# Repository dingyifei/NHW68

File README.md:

# Not Hand Wired 68 Keys

## License

This project (not include ./hardware/KiCad/, ./code, or files with licenses inside them) is using MIT license.

If not specified, the files in ./code are GPL V2

## Code

Code should be functional, haven't push it to QMK or tested on the keyboard yet, compile passed.

## Hardware

I'm attempting to draw the PCB and its my first time drawing a PCB so 0 confidence it will work. I did my research and if you want to use it plz do your own research make sure it works.

I have not yet tested the PCB, the keyboard PCB currently looks like this:

The keyboard uses STM32F303CCT6, IS31FL3733 and have per Key RGB. 

The RGB is optional since it can work without RGB (I believe most people can live without RGB :p)

Here is the fusion 360 3d mode, I think it is good enough

Fusion 360 Link: https://a360.co/2X8L0Fb

**Note: The screws and nuts are downloaded 3D model from misumi, license info can be found on misumi website**

## Layout

The blue keys' function depend on use case

## Assembly

Stacking: 

1. Plate(1.6mm)
2. Spacer(1.2mm)x3
3. PCB(1.6mm)
4. Nuts(2.4mm or more)
5. Spacer(1.2mm)
6. Base(1.6mm)
7. Nuts(2.4mm)

Use 16mm~18mm M3 screw and nuts should be just fine, a PCB fab usually provide 1.6mm and 1.2mm.

Note: Manually cut 2 spacer PCB can replace the 4. Nuts but it would mean you need to choose "Order 10" option in the most fabs (which would increase the difficulty in sourcing all the parts)

## Cost

5 piece of (Spacer, PCB, Plate, Base) - $70 if you choose leaded HSAL

Parts are relatively cheap and you don't have to worry about them, LCSC is a good place to get all those parts(u probably need Amazon for Kailh hot swap, DigiKey for RGB controller)

## Release V1.1 

#### Known Problems

1. Key Caps are hard to find
2. Center is 2u left
3. RGB LED footprint is WRONG and WON'T WORK

4. 0 ESD protection

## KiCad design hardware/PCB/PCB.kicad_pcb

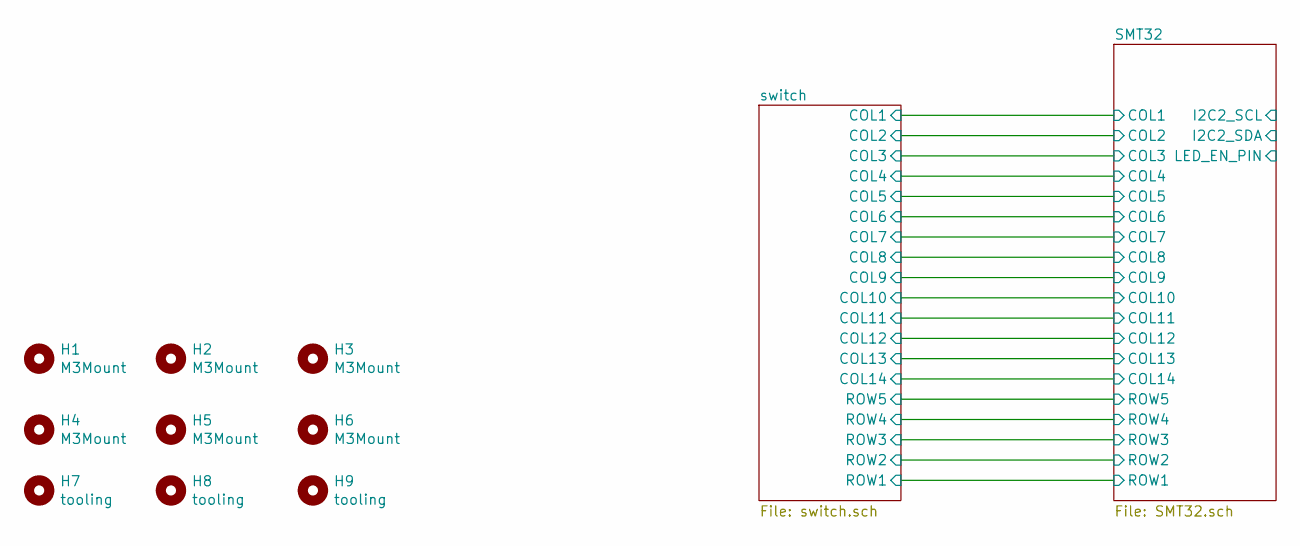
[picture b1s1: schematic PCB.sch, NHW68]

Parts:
H1, H2, H3, H4, H5, H6: M3Mount; MountingHole_3.2mm_M3_DIN965
H7, H8, H9: tooling; JLC_SMT_ToolingHole

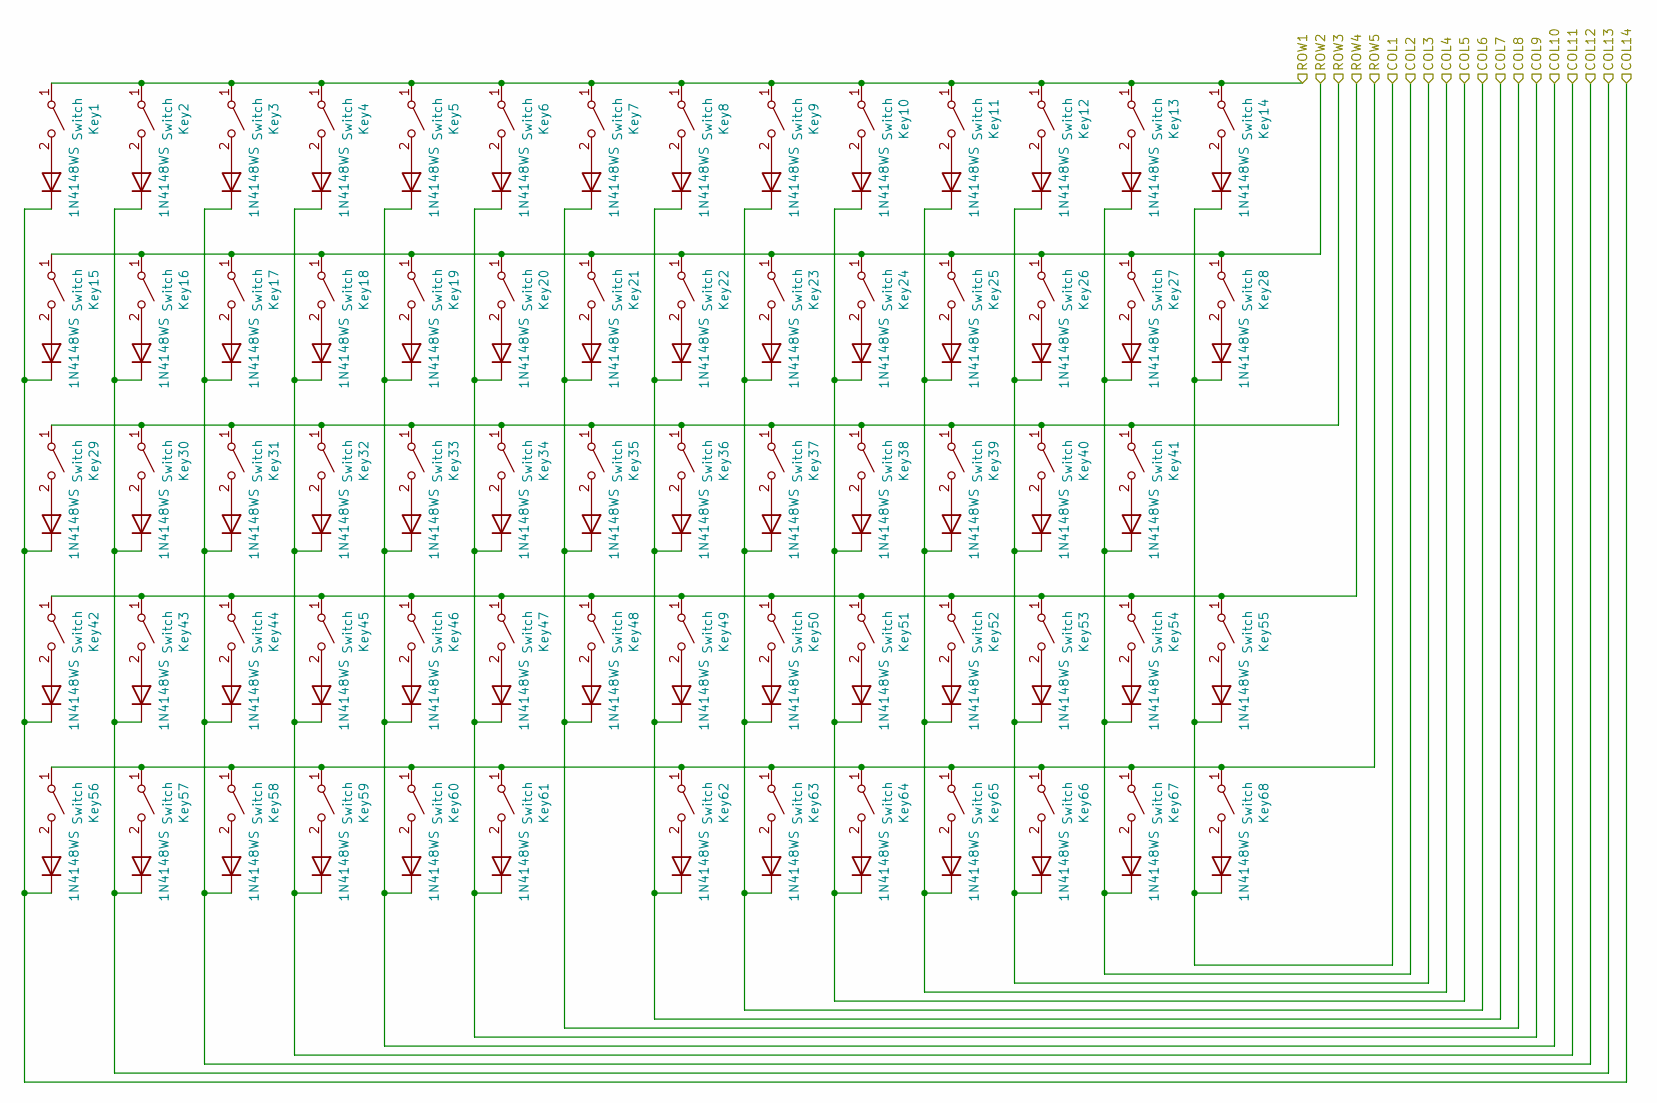
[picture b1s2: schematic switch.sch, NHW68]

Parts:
D1, D2, D3, D4, D5, D6, D7, D8, D9, D10, D11, D12, D13, D14, D15, D16, D17, D18, D19, D20, D21, D22, D23, D24, D25, D26, D27, D28, D29, D30, D31, D32, D33, D34, D35, D36, D37, D38, D39, D40, D41, D42, D43, D44, D45, D46, D47, D48, D49, D50, D51, D52, D53, D54, D55, D56, D57, D58, D59, D60, D61, D62, D63, D64, D65, D66, D67, D68: 1N4148WS; D_SOD-323; Part Number 1N4148WS; LCSC C110221
Key1, Key2, Key3, Key4, Key5, Key6, Key7, Key8, Key9, Key10, Key11, Key12, Key13, Key14, Key15, Key16, Key17, Key18, Key19, Key20, Key21, Key22, Key23, Key24, Key25, Key26, Key27, Key28, Key29, Key30, Key31, Key32, Key33, Key34, Key35, Key36, Key37, Key38, Key39, Key40, Key41, Key42, Key43, Key44, Key45, Key46, Key47, Key48, Key49, Key50, Key51, Key52, Key53, Key54, Key55, Key56, Key57, Key58, Key59, Key60, Key61, Key62, Key63, Key64, Key65, Key66, Key67, Key68: Switch; Kailh_socket_MX_simplified; Part Number CPG151101S11

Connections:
/SMT32/COL1: D14.1 (K), D28.1 (K), D55.1 (K), D68.1 (K); also elsewhere on the board
/SMT32/COL2: D13.1 (K), D27.1 (K), D41.1 (K), D54.1 (K), D67.1 (K); also elsewhere on the board
/SMT32/COL3: D12.1 (K), D26.1 (K), D40.1 (K), D53.1 (K), D66.1 (K); also elsewhere on the board
/SMT32/COL4: D11.1 (K), D25.1 (K), D39.1 (K), D52.1 (K), D65.1 (K); also elsewhere on the board
/SMT32/COL5: D10.1 (K), D24.1 (K), D38.1 (K), D51.1 (K), D64.1 (K); also elsewhere on the board
/SMT32/COL6: D9.1 (K), D23.1 (K), D37.1 (K), D50.1 (K), D63.1 (K); also elsewhere on the board
/SMT32/COL7: D8.1 (K), D22.1 (K), D36.1 (K), D49.1 (K), D62.1 (K); also elsewhere on the board
/SMT32/COL8: D7.1 (K), D21.1 (K), D35.1 (K), D48.1 (K); also elsewhere on the board
/SMT32/COL9: D6.1 (K), D20.1 (K), D34.1 (K), D47.1 (K), D61.1 (K); also elsewhere on the board
/SMT32/COL10: D5.1 (K), D19.1 (K), D33.1 (K), D46.1 (K), D60.1 (K); also elsewhere on the board
/SMT32/COL11: D4.1 (K), D18.1 (K), D32.1 (K), D45.1 (K), D59.1 (K); also elsewhere on the board
/SMT32/COL12: D3.1 (K), D17.1 (K), D31.1 (K), D44.1 (K), D58.1 (K); also elsewhere on the board
/SMT32/COL13: D2.1 (K), D16.1 (K), D30.1 (K), D43.1 (K), D57.1 (K); also elsewhere on the board
/SMT32/COL14: D1.1 (K), D15.1 (K), D29.1 (K), D42.1 (K), D56.1 (K); also elsewhere on the board
/SMT32/ROW1: Key1.1 (A), Key2.1 (A), Key3.1 (A), Key4.1 (A), Key5.1 (A), Key6.1 (A), Key7.1 (A), Key8.1 (A), Key9.1 (A), Key10.1 (A), Key11.1 (A), Key12.1 (A), Key13.1 (A), Key14.1 (A); also elsewhere on the board
/SMT32/ROW2: Key15.1 (A), Key16.1 (A), Key17.1 (A), Key18.1 (A), Key19.1 (A), Key20.1 (A), Key21.1 (A), Key22.1 (A), Key23.1 (A), Key24.1 (A), Key25.1 (A), Key26.1 (A), Key27.1 (A), Key28.1 (A); also elsewhere on the board
/SMT32/ROW3: Key29.1 (A), Key30.1 (A), Key31.1 (A), Key32.1 (A), Key33.1 (A), Key34.1 (A), Key35.1 (A), Key36.1 (A), Key37.1 (A), Key38.1 (A), Key39.1 (A), Key40.1 (A), Key41.1 (A); also elsewhere on the board
/SMT32/ROW4: Key42.1 (A), Key43.1 (A), Key44.1 (A), Key45.1 (A), Key46.1 (A), Key47.1 (A), Key48.1 (A), Key49.1 (A), Key50.1 (A), Key51.1 (A), Key52.1 (A), Key53.1 (A), Key54.1 (A), Key55.1 (A); also elsewhere on the board
/SMT32/ROW5: Key56.1 (A), Key57.1 (A), Key58.1 (A), Key59.1 (A), Key60.1 (A), Key61.1 (A), Key62.1 (A), Key63.1 (A), Key64.1 (A), Key65.1 (A), Key66.1 (A), Key67.1 (A), Key68.1 (A); also elsewhere on the board
unnamed: D1.2 (A), Key1.2 (B)
unnamed: D2.2 (A), Key2.2 (B)
unnamed: D3.2 (A), Key3.2 (B)
unnamed: D4.2 (A), Key4.2 (B)
unnamed: D5.2 (A), Key5.2 (B)
unnamed: D6.2 (A), Key6.2 (B)
unnamed: D7.2 (A), Key7.2 (B)
unnamed: D8.2 (A), Key8.2 (B)
unnamed: D9.2 (A), Key9.2 (B)
unnamed: D10.2 (A), Key10.2 (B)
unnamed: D11.2 (A), Key11.2 (B)
unnamed: D12.2 (A), Key12.2 (B)
unnamed: D13.2 (A), Key13.2 (B)
unnamed: D14.2 (A), Key14.2 (B)
unnamed: D15.2 (A), Key15.2 (B)
unnamed: D16.2 (A), Key16.2 (B)
unnamed: D17.2 (A), Key17.2 (B)
unnamed: D18.2 (A), Key18.2 (B)
unnamed: D19.2 (A), Key19.2 (B)
unnamed: D20.2 (A), Key20.2 (B)
unnamed: D21.2 (A), Key21.2 (B)
unnamed: D22.2 (A), Key22.2 (B)
unnamed: D23.2 (A), Key23.2 (B)
unnamed: D24.2 (A), Key24.2 (B)
unnamed: D25.2 (A), Key25.2 (B)
unnamed: D26.2 (A), Key26.2 (B)
unnamed: D27.2 (A), Key27.2 (B)
unnamed: D28.2 (A), Key28.2 (B)
unnamed: D29.2 (A), Key29.2 (B)
unnamed: D30.2 (A), Key30.2 (B)
unnamed: D31.2 (A), Key31.2 (B)
unnamed: D32.2 (A), Key32.2 (B)
unnamed: D33.2 (A), Key33.2 (B)
unnamed: D34.2 (A), Key34.2 (B)
unnamed: D35.2 (A), Key35.2 (B)
unnamed: D36.2 (A), Key36.2 (B)
unnamed: D37.2 (A), Key37.2 (B)
unnamed: D38.2 (A), Key38.2 (B)
unnamed: D39.2 (A), Key39.2 (B)
unnamed: D40.2 (A), Key40.2 (B)
unnamed: D41.2 (A), Key41.2 (B)
unnamed: D42.2 (A), Key42.2 (B)
unnamed: D43.2 (A), Key43.2 (B)
unnamed: D44.2 (A), Key44.2 (B)
unnamed: D45.2 (A), Key45.2 (B)
unnamed: D46.2 (A), Key46.2 (B)
unnamed: D47.2 (A), Key47.2 (B)
unnamed: D48.2 (A), Key48.2 (B)
unnamed: D49.2 (A), Key49.2 (B)
unnamed: D50.2 (A), Key50.2 (B)
unnamed: D51.2 (A), Key51.2 (B)
unnamed: D52.2 (A), Key52.2 (B)
unnamed: D53.2 (A), Key53.2 (B)
unnamed: D54.2 (A), Key54.2 (B)
unnamed: D55.2 (A), Key55.2 (B)
unnamed: D56.2 (A), Key56.2 (B)
unnamed: D57.2 (A), Key57.2 (B)
unnamed: D58.2 (A), Key58.2 (B)
unnamed: D59.2 (A), Key59.2 (B)
unnamed: D60.2 (A), Key60.2 (B)
unnamed: D61.2 (A), Key61.2 (B)
unnamed: D62.2 (A), Key62.2 (B)
unnamed: D63.2 (A), Key63.2 (B)
unnamed: D64.2 (A), Key64.2 (B)
unnamed: D65.2 (A), Key65.2 (B)
unnamed: D66.2 (A), Key66.2 (B)
unnamed: D67.2 (A), Key67.2 (B)
unnamed: D68.2 (A), Key68.2 (B)

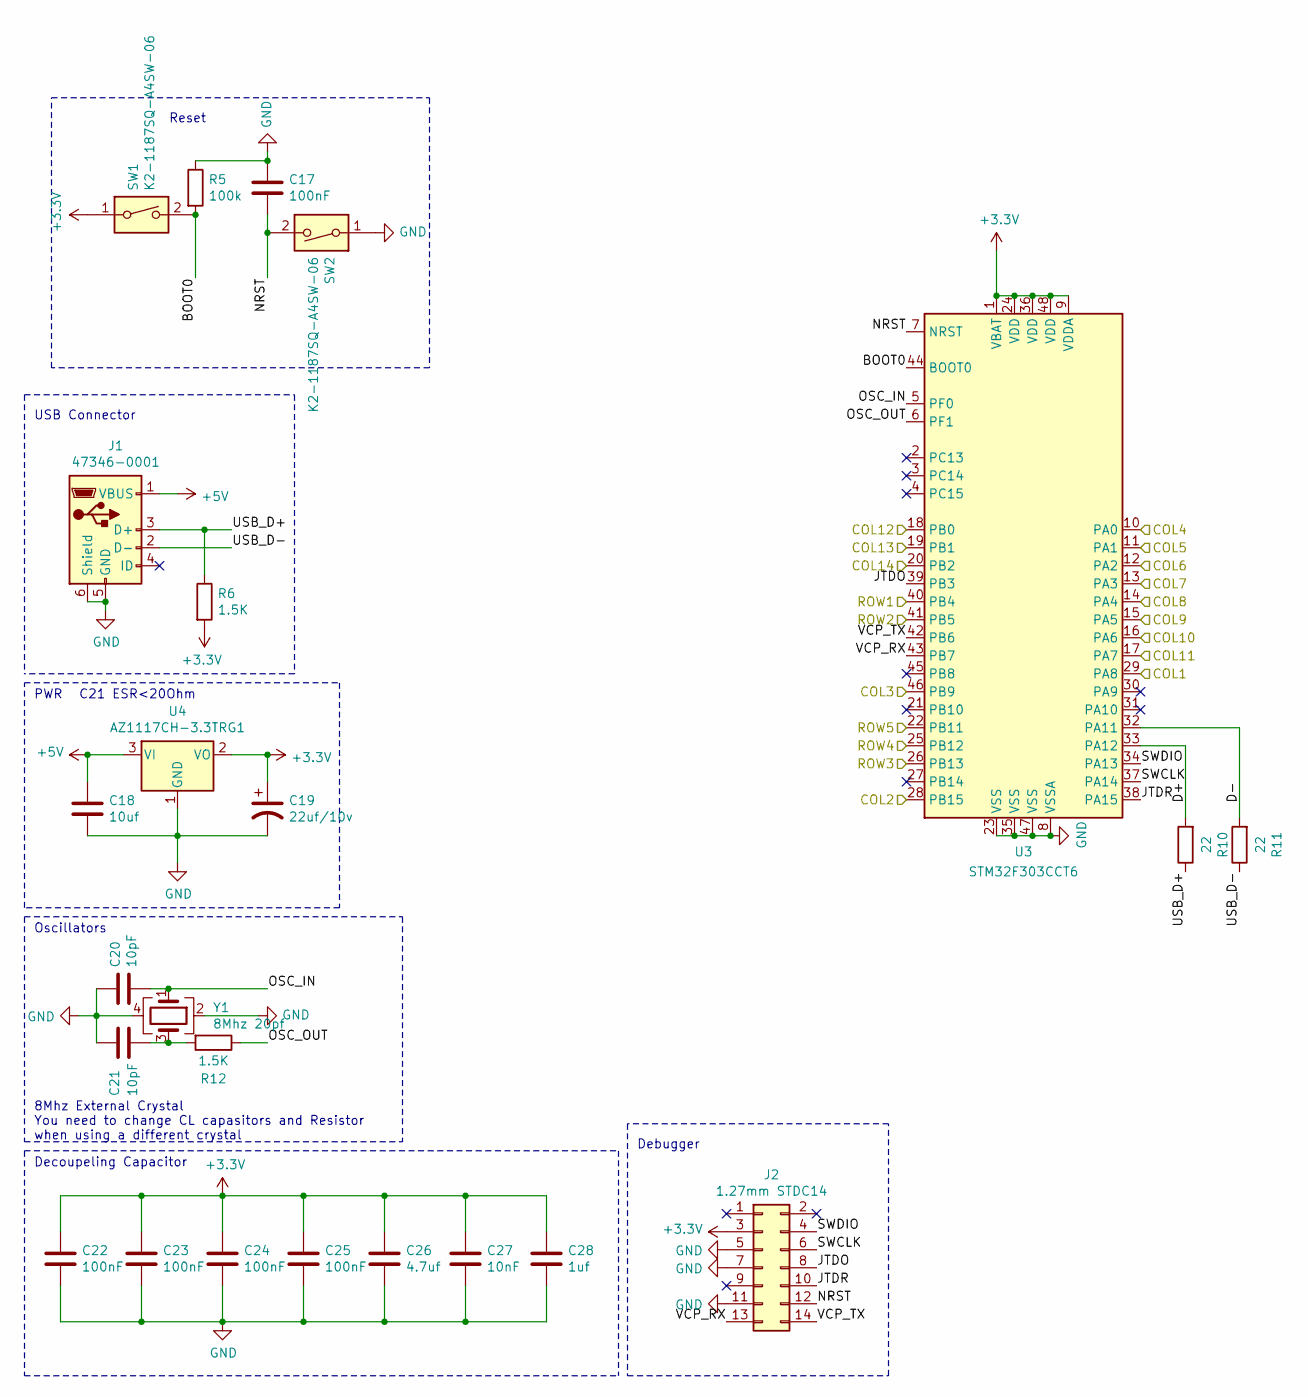
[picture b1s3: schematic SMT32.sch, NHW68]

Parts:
C17, C22, C23, C24, C25: 100nF; C_0603_1608Metric; Part Number 0603B104K160CT; LCSC C80516
C18: 10uf; C_0603_1608Metric; Part Number 0603X106K100NT; LCSC C38898
C19: 22uf/10v; CP_EIA-3216-18_Kemet-A; Part Number TAJA226K010RNJ; LCSC C11366
C20, C21: 10pF; C_0603_1608Metric; Part Number CC0603GRNPO9BN100; LCSC C325468
C26: 4.7uf; C_0603_1608Metric; Part Number CL10A475KA8NQNC; LCSC C69335
C27: 10nF; C_0603_1608Metric; Part Number CL10B103JB8NNNC; LCSC C7248
C28: 1uf; C_0603_1608Metric; Part Number UMK107AB7105KA-T; LCSC C105174
J1: 47346-0001; USB_Micro-B_Molex_47346-0001; Part Number 47346-0001; LCSC C132560
J2: 1.27mm STDC14; PinHeader_2x07_P1.27mm_Vertical
R5: 100k; R_0603_1608Metric; Part Number CR0603FA1003G; LCSC C100703
R6, R12: 1.5K; R_0603_1608Metric; Part Number RTT031501FTP; LCSC C103303
R10, R11: 22; R_0603_1608Metric; Part Number CR0603FA22R0G; LCSC C100876
SW1, SW2: K2-1187SQ-A4SW-06; Part Number K2-1187SQ-A4SW-06; LCSC C92584
U3: STM32F303CCT6; LQFP-48_7x7mm_P0.5mm; Part Number STM32F303CCT6; LCSC C81523
U4: AZ1117CH-3.3TRG1; SOT-223-3_TabPin2; Part Number AZ1117CH-3.3TRG1; LCSC C92102
Y1: 8Mhz 20pf; Crystal_SMD_3225-4Pin_3.2x2.5mm; Part Number TAXM8M4RDBCCT2T; LCSC C400090

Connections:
+3V3: C19.1, C22.1, C23.1, C24.1, C25.1, C26.1, C27.1, C28.1, J2.3, R6.2, SW1.1, U3.1 (VBAT), U3.9 (VDDA), U3.24 (VDD), U3.36 (VDD), U3.48 (VDD), U4.2 (VO)
+5V: C18.1, J1.1 (VBUS), U4.3 (VI)
/SMT32/BOOT0: R5.2, SW1.2, U3.44 (BOOT0)
/SMT32/COL1: U3.29 (PA8); also elsewhere on the board
/SMT32/COL2: U3.28 (PB15); also elsewhere on the board
/SMT32/COL3: U3.46 (PB9); also elsewhere on the board
/SMT32/COL4: U3.10 (PA0); also elsewhere on the board
/SMT32/COL5: U3.11 (PA1); also elsewhere on the board
/SMT32/COL6: U3.12 (PA2); also elsewhere on the board
/SMT32/COL7: U3.13 (PA3); also elsewhere on the board
/SMT32/COL8: U3.14 (PA4); also elsewhere on the board
/SMT32/COL9: U3.15 (PA5); also elsewhere on the board
/SMT32/COL10: U3.16 (PA6); also elsewhere on the board
/SMT32/COL11: U3.17 (PA7); also elsewhere on the board
/SMT32/COL12: U3.18 (PB0); also elsewhere on the board
/SMT32/COL13: U3.19 (PB1); also elsewhere on the board
/SMT32/COL14: U3.20 (PB2); also elsewhere on the board
/SMT32/D+: R10.2, U3.33 (PA12)
/SMT32/D-: R11.2, U3.32 (PA11)
/SMT32/JTDO: J2.8, U3.39 (PB3)
/SMT32/JTDR: J2.10, U3.38 (PA15)
/SMT32/NRST: C17.2, J2.12, SW2.2, U3.7 (NRST)
/SMT32/OSC_IN: C20.2, U3.5 (PF0), Y1.1
/SMT32/OSC_OUT: R12.1, U3.6 (PF1)
/SMT32/ROW1: U3.40 (PB4); also elsewhere on the board
/SMT32/ROW2: U3.41 (PB5); also elsewhere on the board
/SMT32/ROW3: U3.26 (PB13); also elsewhere on the board
/SMT32/ROW4: U3.25 (PB12); also elsewhere on the board
/SMT32/ROW5: U3.22 (PB11); also elsewhere on the board
/SMT32/SWCLK: J2.6, U3.37 (PA14)
/SMT32/SWDIO: J2.4, U3.34 (PA13)
/SMT32/USB_D+: J1.3 (D+), R6.1, R10.1
/SMT32/USB_D-: J1.2 (D-), R11.1
/SMT32/VCP_RX: J2.13, U3.43 (PB7)
/SMT32/VCP_TX: J2.14, U3.42 (PB6)
GND: C17.1, C18.2, C19.2, C20.1, C21.1, C22.2, C23.2, C24.2, C25.2, C26.2, C27.2, C28.2, J1.5 (GND), J1.6 (Shield), J2.5, J2.7, J2.11, R5.1, SW2.1, U3.8 (VSSA), U3.23 (VSS), U3.35 (VSS), U3.47 (VSS), U4.1 (GND), Y1.2, Y1.4
unnamed: C21.2, R12.2, Y1.3

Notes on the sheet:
PWR
C21 ESR<20Ohm
8Mhz External Crystal You need to change CL capasitors and Resistor when using a different crystal
USB Connector
Oscillators
Decoupeling Capacitor
Debugger
Reset

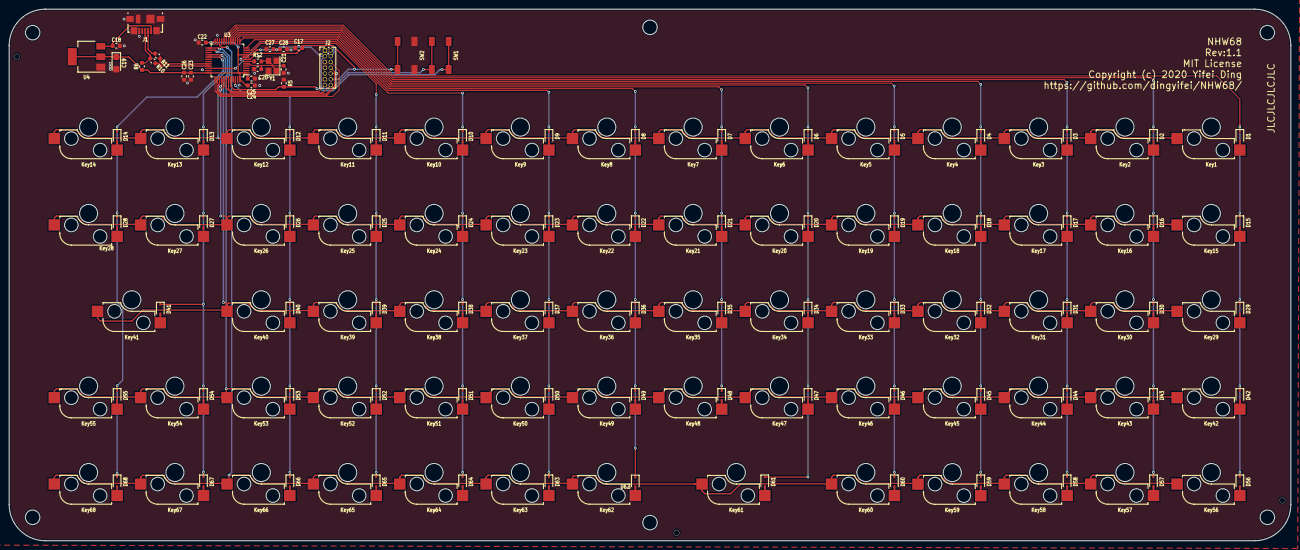
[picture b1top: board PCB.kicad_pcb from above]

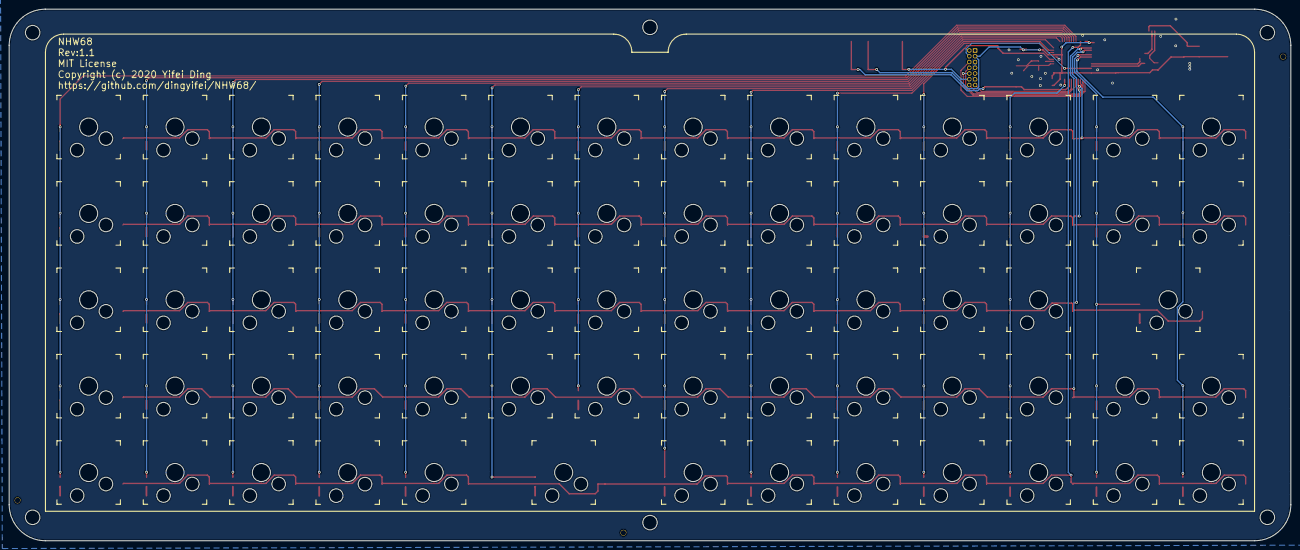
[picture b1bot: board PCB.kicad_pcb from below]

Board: 2 copper layers, 282.7 x 117.3 mm, 169 parts (68 on the bottom side), 105 nets.

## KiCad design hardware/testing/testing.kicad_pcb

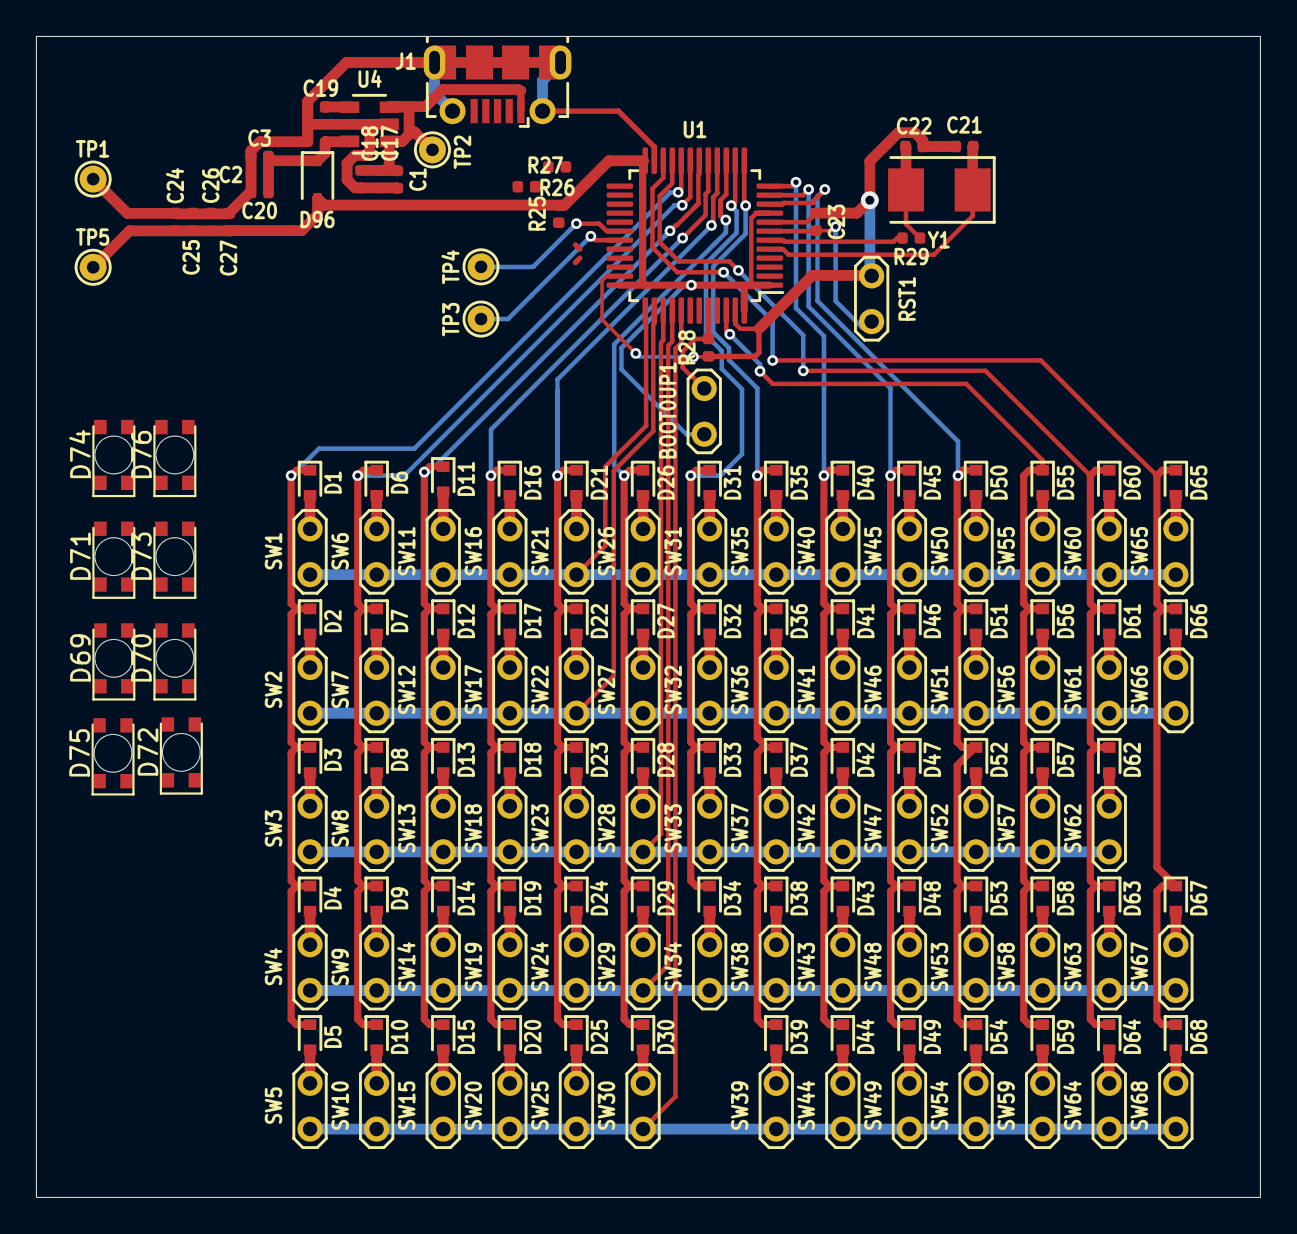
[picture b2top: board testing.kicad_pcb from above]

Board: 2 copper layers, 68.0 x 64.5 mm, 175 parts (0 on the bottom side), 103 nets.

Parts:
BOOT0UP1: SW_DIP_x01; TestPoint_2Pads_Pitch2.54mm_Drill0.8mm
C1, C3: 10uF; C_0402_1005Metric
C2, C18, C24, C25, C26, C27: 100nF; C_0402_1005Metric
C17, C20, C23: 1uF; C_0402_1005Metric
C19: 10nF; C_0402_1005Metric
C21, C22: 20pF; C_0402_1005Metric
D1, D2, D3, D4, D5, D6, D7, D8, D9, D10, D11, D12, D13, D14, D15, D16, D17, D18, D19, D20, D21, D22, D23, D24, D25, D26, D27, D28, D29, D30, D31, D32, D33, D34, D35, D36, D37, D38, D39, D40, D41, D42, D43, D44, D45, D46, D47, D48, D49, D50, D51, D52, D53, D54, D55, D56, D57, D58, D59, D60, D61, D62, D63, D64, D65, D66, D67, D68: 1N4148WT; D_SOD-523
D69, D70, D71, D72, D73, D74, D75, D76: MHT150RGBCT; LED_1206_3216Metric
D96: BAT60JFILM; D_SOD-323
J1: USB_B_Micro; USB_Micro-B_Molex-105017-0001
R25: 1.5K; R_0402_1005Metric
R26, R27: 22; R_0402_1005Metric
R28: 100K; R_0402_1005Metric
R29: 1K; R_0402_1005Metric
RST1: SW_DIP_x01; TestPoint_2Pads_Pitch2.54mm_Drill0.8mm
SW1, SW2, SW3, SW4, SW5, SW6, SW7, SW8, SW9, SW10, SW11, SW12, SW13, SW14, SW15, SW16, SW17, SW18, SW19, SW20, SW21, SW22, SW23, SW24, SW25, SW26, SW27, SW28, SW29, SW30, SW31, SW32, SW33, SW34, SW35, SW36, SW37, SW38, SW39, SW40, SW41, SW42, SW43, SW44, SW45, SW46, SW47, SW48, SW49, SW50, SW51, SW52, SW53, SW54, SW55, SW56, SW57, SW58, SW59, SW60, SW61, SW62, SW63, SW64, SW65, SW66, SW67, SW68: SW; TestPoint_2Pads_Pitch2.54mm_Drill0.8mm
TP1, TP2, TP3, TP4, TP5: TestPoint; TestPoint_THTPad_D1.5mm_Drill0.7mm
U1: STM32F303CCT6; LQFP-48_7x7mm_P0.5mm
U4: LD3985M33R; SOT-23-5
Y1: 8Mhz 20PF; Crystal_SMD_5032-2Pin_5.0x3.2mm

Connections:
+3V3: BOOT0UP1.1, C24.1, C25.1, C26.1, C27.1, D96.2, R25.2, TP5.1, U1.1, U1.9, U1.24, U1.36, U1.48
+5V: C1.1, C17.1, C18.1, J1.1, TP2.1, U4.1, U4.3
/SMT32/COL1: D65.1, D66.1, D67.1, D68.1, U1.22
/SMT32/COL2: D60.1, D61.1, D62.1, D63.1, D64.1, U1.21
/SMT32/COL3: D55.1, D56.1, D57.1, D58.1, D59.1, U1.46
/SMT32/COL4: D50.1, D51.1, D52.1, D53.1, D54.1, U1.10
/SMT32/COL5: D45.1, D46.1, D47.1, D48.1, D49.1, U1.11
/SMT32/COL6: D40.1, D41.1, D42.1, D43.1, D44.1, U1.12
/SMT32/COL7: D35.1, D36.1, D37.1, D38.1, D39.1, U1.13
/SMT32/COL8: D31.1, D32.1, D33.1, D34.1, U1.14
/SMT32/COL9: D26.1, D27.1, D28.1, D29.1, D30.1, U1.15
/SMT32/COL10: D21.1, D22.1, D23.1, D24.1, D25.1, U1.16
/SMT32/COL11: D16.1, D17.1, D18.1, D19.1, D20.1, U1.17
/SMT32/COL12: D11.1, D12.1, D13.1, D14.1, D15.1, U1.18
/SMT32/COL13: D6.1, D7.1, D8.1, D9.1, D10.1, U1.19
/SMT32/COL14: D1.1, D2.1, D3.1, D4.1, D5.1, U1.20
/SMT32/ROW1: SW1.1, SW6.1, SW11.1, SW16.1, SW21.1, SW26.1, SW31.1, SW35.1, SW40.1, SW45.1, SW50.1, SW55.1, SW60.1, SW65.1, U1.37
/SMT32/ROW2: SW2.1, SW7.1, SW12.1, SW17.1, SW22.1, SW27.1, SW32.1, SW36.1, SW41.1, SW46.1, SW51.1, SW56.1, SW61.1, SW66.1, U1.38
/SMT32/ROW3: SW3.1, SW8.1, SW13.1, SW18.1, SW23.1, SW28.1, SW33.1, SW37.1, SW42.1, SW47.1, SW52.1, SW57.1, SW62.1, U1.39
/SMT32/ROW4: SW4.1, SW9.1, SW14.1, SW19.1, SW24.1, SW29.1, SW34.1, SW38.1, SW43.1, SW48.1, SW53.1, SW58.1, SW63.1, SW67.1, U1.40
/SMT32/ROW5: SW5.1, SW10.1, SW15.1, SW20.1, SW25.1, SW30.1, SW39.1, SW44.1, SW49.1, SW54.1, SW59.1, SW64.1, SW68.1, U1.41
/SMT32/USB_D+: J1.3, R25.1, R27.1
/SMT32/USB_D-: J1.2, R26.2
GND: C1.2, C2.2, C3.2, C17.2, C18.2, C19.2, C20.2, C21.1, C22.1, C23.1, C24.2, C25.2, C26.2, C27.2, J1.5, J1.6, R28.1, RST1.1, TP1.1, U1.8, U1.23, U1.35, U1.47, U4.2
unnamed: BOOT0UP1.2, R28.2, U1.44
unnamed: C2.1, C3.1, C20.1, D96.1, U4.5
unnamed: C19.1, U4.4
unnamed: C21.2, U1.5, Y1.1
unnamed: C22.2, R29.2, Y1.2
unnamed: C23.2, RST1.2, U1.7
unnamed: D1.2, SW1.2
unnamed: D2.2, SW2.2
unnamed: D3.2, SW3.2
unnamed: D4.2, SW4.2
unnamed: D5.2, SW5.2
unnamed: D6.2, SW6.2
unnamed: D7.2, SW7.2
unnamed: D8.2, SW8.2
unnamed: D9.2, SW9.2
unnamed: D10.2, SW10.2
unnamed: D11.2, SW11.2
unnamed: D12.2, SW12.2
unnamed: D13.2, SW13.2
unnamed: D14.2, SW14.2
unnamed: D15.2, SW15.2
unnamed: D16.2, SW16.2
unnamed: D17.2, SW17.2
unnamed: D18.2, SW18.2
unnamed: D19.2, SW19.2
unnamed: D20.2, SW20.2
unnamed: D21.2, SW21.2
unnamed: D22.2, SW22.2
unnamed: D23.2, SW23.2
unnamed: D24.2, SW24.2
unnamed: D25.2, SW25.2
unnamed: D26.2, SW26.2
unnamed: D27.2, SW27.2
unnamed: D28.2, SW28.2
unnamed: D29.2, SW29.2
unnamed: D30.2, SW30.2
unnamed: D31.2, SW31.2
unnamed: D32.2, SW32.2
unnamed: D33.2, SW33.2
unnamed: D34.2, SW34.2
unnamed: D35.2, SW35.2
unnamed: D36.2, SW36.2
unnamed: D37.2, SW37.2
unnamed: D38.2, SW38.2
unnamed: D39.2, SW39.2
unnamed: D40.2, SW40.2
unnamed: D41.2, SW41.2
unnamed: D42.2, SW42.2
unnamed: D43.2, SW43.2
unnamed: D44.2, SW44.2
unnamed: D45.2, SW45.2
unnamed: D46.2, SW46.2
unnamed: D47.2, SW47.2
unnamed: D48.2, SW48.2
unnamed: D49.2, SW49.2
unnamed: D50.2, SW50.2
unnamed: D51.2, SW51.2
unnamed: D52.2, SW52.2
unnamed: D53.2, SW53.2
unnamed: D54.2, SW54.2
unnamed: D55.2, SW55.2
unnamed: D56.2, SW56.2
unnamed: D57.2, SW57.2
unnamed: D58.2, SW58.2
unnamed: D59.2, SW59.2
unnamed: D60.2, SW60.2
unnamed: D61.2, SW61.2
unnamed: D62.2, SW62.2
unnamed: D63.2, SW63.2
unnamed: D64.2, SW64.2
unnamed: D65.2, SW65.2
unnamed: D66.2, SW66.2
unnamed: D67.2, SW67.2
unnamed: D68.2, SW68.2
unnamed: R26.1, U1.32
unnamed: R27.2, U1.33
unnamed: R29.1, U1.6
unnamed: TP3.1, U1.31
unnamed: TP4.1, U1.30

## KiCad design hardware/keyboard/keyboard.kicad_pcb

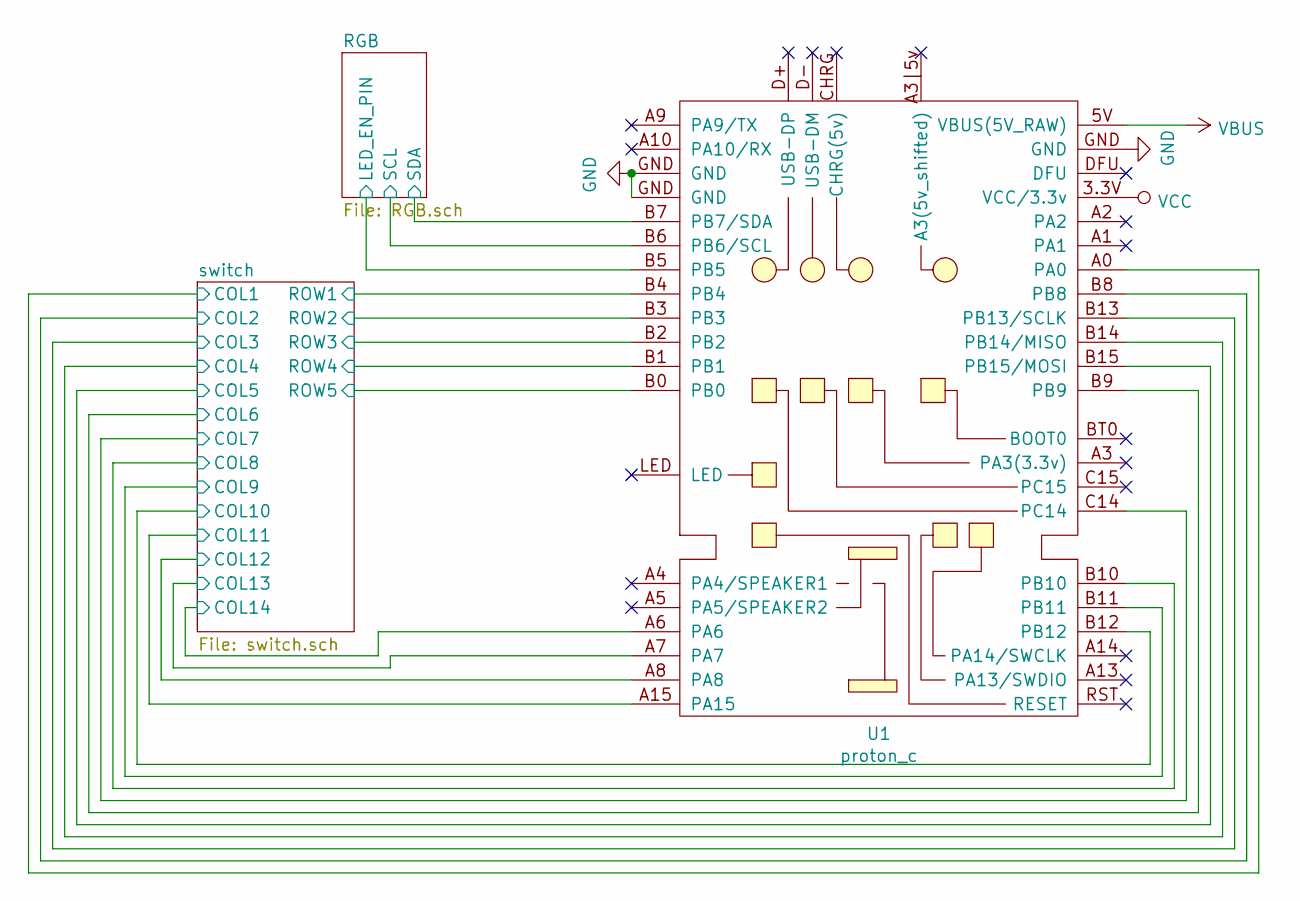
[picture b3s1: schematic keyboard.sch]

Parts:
U1: proton_c; PROTON-C-THT-SPEAKER

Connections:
/RGB/LED_EN_PIN: U1.B5; also elsewhere on the board
/RGB/SCL: U1.B6 (PB6/SCL); also elsewhere on the board
/RGB/SDA: U1.B7 (PB7/SDA); also elsewhere on the board
/switch/COL1: U1.A1; also elsewhere on the board
/switch/COL2: U1.A0; also elsewhere on the board
/switch/COL3: U1.B8; also elsewhere on the board
/switch/COL4: U1.B13 (PB13/SCLK); also elsewhere on the board
/switch/COL5: U1.B14 (PB14/MISO); also elsewhere on the board
/switch/COL6: U1.B15 (PB15/MOSI); also elsewhere on the board
/switch/COL7: U1.B9; also elsewhere on the board
/switch/COL8: U1.B10; also elsewhere on the board
/switch/COL9: U1.B11; also elsewhere on the board
/switch/COL10: U1.B12; also elsewhere on the board
/switch/COL11: U1.A15; also elsewhere on the board
/switch/COL12: U1.A8; also elsewhere on the board
/switch/COL13: U1.A7; also elsewhere on the board
/switch/COL14: U1.A6; also elsewhere on the board
/switch/ROW1: U1.B4; also elsewhere on the board
/switch/ROW2: U1.B3; also elsewhere on the board
/switch/ROW3: U1.B2; also elsewhere on the board
/switch/ROW4: U1.B1; also elsewhere on the board
/switch/ROW5: U1.B0; also elsewhere on the board
GND: U1.GND; also elsewhere on the board
VBUS: U1.5V (VBUS(5V_RAW)); also elsewhere on the board
VCC: U1.3.3V (VCC/3.3v); also elsewhere on the board

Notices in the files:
codes/ChibiOS_Board/board.h:
ChibiOS - Copyright (C) 2006..2018 Giovanni Di Sirio
Licensed under the Apache License, Version 2.0 (the "License");
hardware/PCB/PCB.kicad_pcb:
Copyright (c) 2020 Yifei Ding
